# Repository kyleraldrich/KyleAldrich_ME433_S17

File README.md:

# KyleAldrich_ME433_S17

Kyle Aldrich
Northwestern University
ME 433 - Advanced Mechatronics Course

This Repo contains Homework assignments as well as the final project for NU's advanced mechatronics course

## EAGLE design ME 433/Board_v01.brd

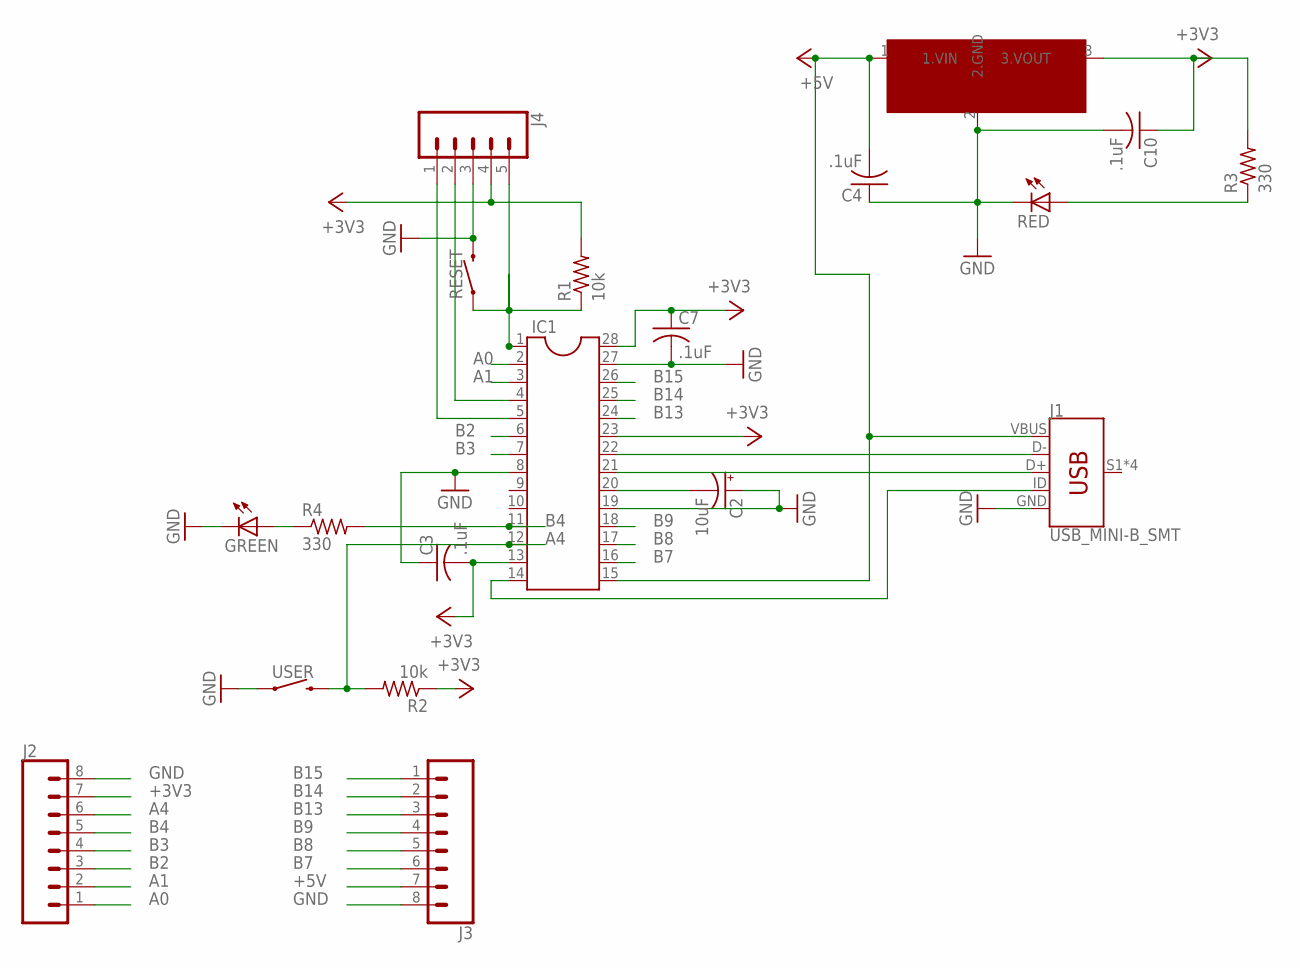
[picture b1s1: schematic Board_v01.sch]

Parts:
C2: 10uF; CT7343
C3, C4, C7, C10: .1uF; C025-025X050
GREEN: LED3MM
IC1: DIL28-3
J1: USB_MINI-B_SMT; USB-MINIB
J2, J3: CONN_08"; 1X08
J4: CONN_05; 1X05
R1, R2: 10k; 0204/5
R3, R4: 330; 0204/5
RED: LED3MM
RESET: MOMENTARY-SWITCH-SPST-PTH-6.0MM; TACTILE_SWITCH_PTH_6.0MM
U$1: MCP1702; TO92
USER: MOMENTARY-SWITCH-SPST-PTH-6.0MM; TACTILE_SWITCH_PTH_6.0MM

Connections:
+3V3: C3.2, C7.1, C10.1, IC1.13, IC1.23, IC1.28, J2.7, J4.4, R1.2, R2.1, R3.2, U$1.3 (3.VOUT)
+5V: C4.2, IC1.15, J1.VBUS, J3.7, U$1.1 (1.VIN)
A0: IC1.2, J2.1
A1: IC1.3, J2.2
A4: IC1.12, J2.6, R2.2, USER.3 (2)
B2: IC1.6, J2.3
B3: IC1.7, J2.4
B4: IC1.11, J2.5, R4.2
B7: IC1.16, J3.6
B8: IC1.17, J3.5
B9: IC1.18, J3.4
B13: IC1.24, J3.3
B14: IC1.25, J3.2
B15: IC1.26, J3.1
GND: C2.+, C3.1, C4.1, C7.2, C10.2, GREEN.K (C), IC1.8, IC1.19, IC1.27, J1.GND, J2.8, J3.8, J4.3, RED.K (C), RESET.3 (2), U$1.2 (2.GND), USER.1
unnamed: IC1.1, J4.5, R1.1, RESET.1
unnamed: IC1.4, J4.2
unnamed: IC1.5, J4.1
unnamed: IC1.22, J1.D-
unnamed: IC1.21, J1.D+
unnamed: IC1.14, J1.ID
unnamed: C2.-, IC1.20
unnamed: GREEN.A, R4.1
unnamed: R3.1, RED.A

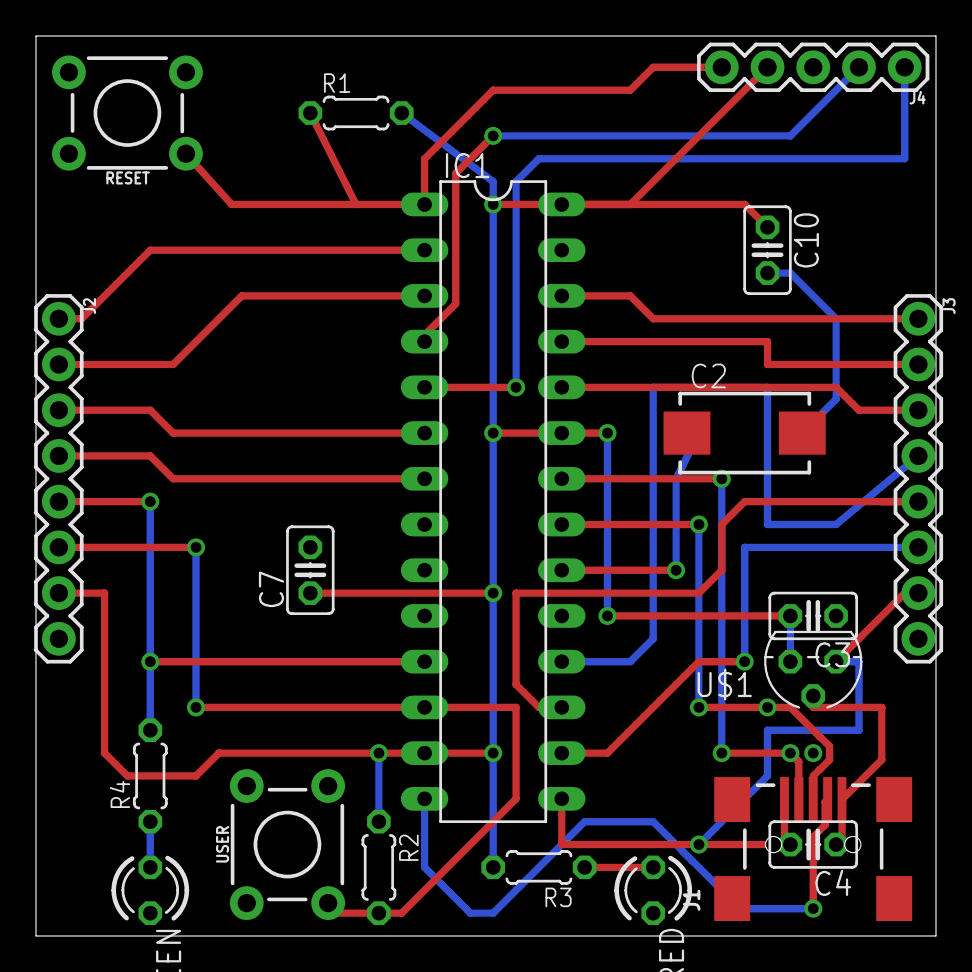
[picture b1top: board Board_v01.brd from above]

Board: 2 copper layers, 50.0 x 50.0 mm, 19 parts (0 on the bottom side), 24 nets.

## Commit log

2017-03-29 :confetti_ball: Added .gitattributes & .gitignore files
2017-03-29 First Commit/Sync
    Come and take it.
2017-03-29 Copied main.c example file
2017-03-29 DEVCFG0 filled in
2017-03-29 DEVCFG1 DONE
2017-03-29 devcfg2 done - uncertain on USB clck
    "hint" for UPLLIDIV says to divide 8MHz then multiply by 12 to get
    48MHz, but there is only one line. Assuming that the multiplication is
    done in other code?
2017-03-29 devcfg3 done
2017-03-30 Using proper IDE now
2017-03-30 Code complete untested
2017-03-30 Fixed Window size typo - Documentation is incorrect: WISZ_25 should be WINSZ_25 Error: Unable to connect to target device, failed to get device ID
2017-03-30 DONE
2017-03-30 Changed to the actual IDE so weird commits here
2017-03-30 playing with the button
2017-03-30 video added
2017-04-06 Completely forgot about Git
    I was doing everything in a different folder.
2017-05-04 I'm back
